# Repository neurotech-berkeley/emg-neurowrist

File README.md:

# emg-neurowrist
Building an EMG-wristband

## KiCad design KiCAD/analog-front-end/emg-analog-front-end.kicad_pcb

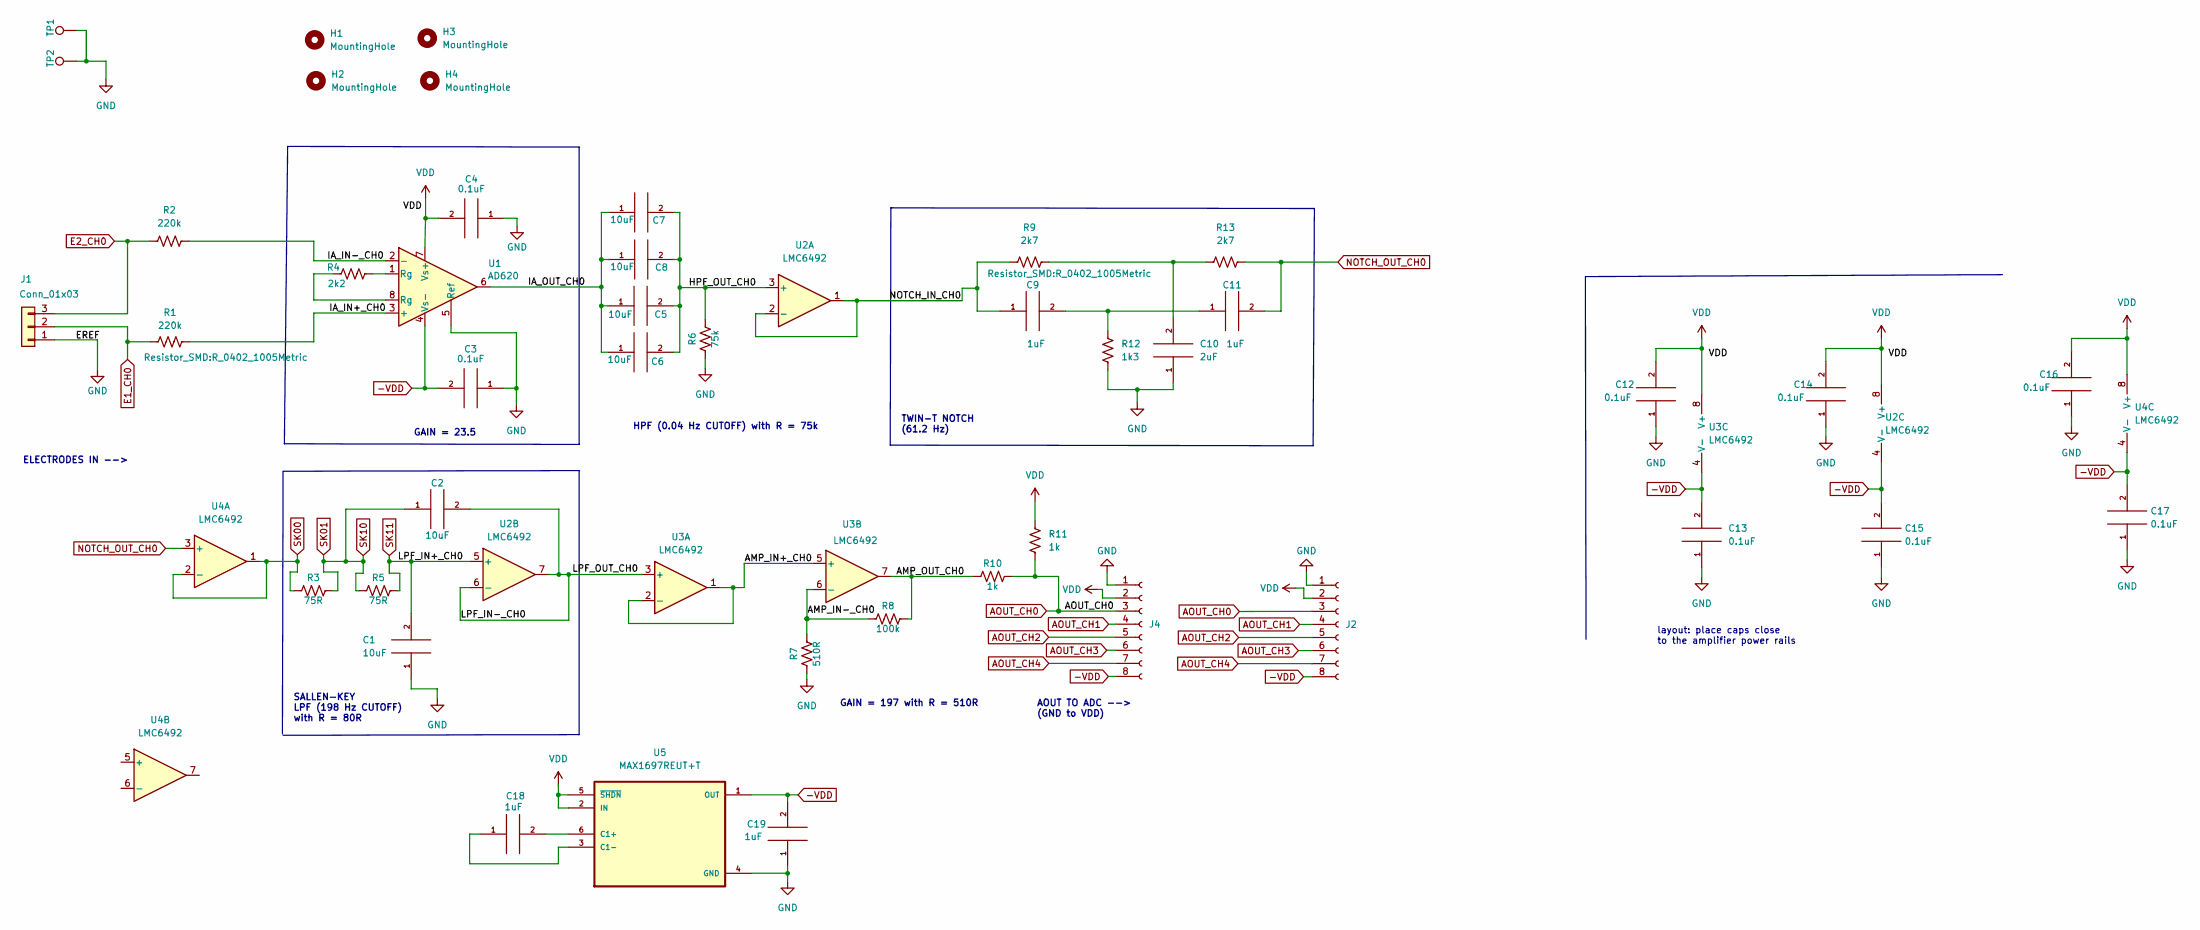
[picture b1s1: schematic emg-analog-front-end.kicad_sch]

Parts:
C1, C2, C5, C6, C7, C8: 10uF; C_0402_1005Metric
C3, C4, C12, C13, C14, C15, C16, C17: 0.1uF; C_0402_1005Metric
C9, C11, C18, C19: 1uF; C_0402_1005Metric
C10: 2uF; C_0402_1005Metric
H1, H2, H3, H4: MountingHole; MountingHole_2.2mm_M2
J1: Conn_01x03; PinHeader_1x03_P1.27mm_Vertical
J2, J4: Conn_01x08_Female; PinHeader_1x08_P1.27mm_Vertical
R1, R2: 220k; R_0402_1005Metric
R3, R5: 75R; R_0402_1005Metric
R4: 2k2; R_0402_1005Metric
R6: 75k; R_0402_1005Metric
R7: 510R; R_0402_1005Metric
R8: 100k; R_0402_1005Metric
R9, R13: 2k7; R_0402_1005Metric
R10, R11: 1k; R_0402_1005Metric
R12: 1k3; R_0402_1005Metric
TP1, TP2: TestPoint; TestPoint_Pad_1.0x1.0mm
U1: AD620; SOIC-8_3.9x4.9mm_P1.27mm
U2, U3, U4: LMC6492; SOIC-8_3.9x4.9mm_P1.27mm
U5: MAX1697REUT+T; SOT95P280X145-6N

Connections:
-VDD: C3.2, C13.2, C15.2, C17.2, C19.2, J2.8, J4.8, U1.4 (Vs-), U2.4 (V-), U3.4 (V-), U4.4 (V-), U5.1 (OUT)
/AMP_IN+_CH0: U3.1, U3.2 (-), U3.5 (+)
/AMP_IN-_CH0: R7.1, R8.2, U3.6 (-)
/AMP_OUT_CH0: R8.1, R10.2, U3.7
/HPF_OUT_CH0: C5.2, C6.2, C7.2, C8.2, R6.1, U2.3 (+)
/IA_IN+_CH0: R1.2, U1.3 (+)
/IA_IN-_CH0: R2.2, U1.2 (-)
/IA_OUT_CH0: C5.1, C6.1, C7.1, C8.1, U1.6
/LPF_IN-_CH0: C2.2, U2.6 (-), U2.7, U3.3 (+)
/NOTCH_IN_CH0: C9.1, R9.2, U2.1, U2.2 (-)
AOUT_CH0: J2.3, J4.3, R10.1, R11.1
AOUT_CH1: J2.4, J4.4
AOUT_CH2: J2.5, J4.5
AOUT_CH3: J2.6, J4.6
AOUT_CH4: J2.7, J4.7
E1_CH0: J1.2, R1.1
E2_CH0: J1.3, R2.1
GND: C1.1, C3.1, C4.1, C10.1, C12.1, C13.1, C14.1, C15.1, C16.1, C17.1, C19.1, J1.1, J2.1, J4.1, R6.2, R7.2, R12.2, TP1.1, TP2.1, U1.5 (Ref), U5.4 (GND)
NOTCH_OUT_CH0: C11.2, R13.1, U4.3 (+)
unnamed: C10.2, R9.1, R13.2
unnamed: C9.2, C11.1, R12.1
unnamed: C18.1, U5.3 (C1-)
unnamed: C18.2, U5.6 (C1+)
unnamed: R4.1, U1.1 (Rg)
unnamed: R4.2, U1.8 (Rg)
SK00: R3.2, U4.1, U4.2 (-)
SK01: C2.1, R3.1, R5.2
SK11: C1.2, R5.1, U2.5 (+)
VDD: C4.2, C12.2, C14.2, C16.2, J2.2, J4.2, R11.2, U1.7 (Vs+), U2.8 (V+), U3.8 (V+), U4.8 (V+), U5.2 (IN), U5.5 (~SHDN)

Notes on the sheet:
GAIN = 23.5
TWIN-T NOTCH (61.2 Hz)
layout: place caps close to the amplifier power rails
HPF (0.04 Hz CUTOFF) with R = 75k
GAIN = 197 with R = 510R
SALLEN-KEY LPF (198 Hz CUTOFF) with R = 80R
ELECTRODES IN -->
AOUT TO ADC --> (GND to VDD)

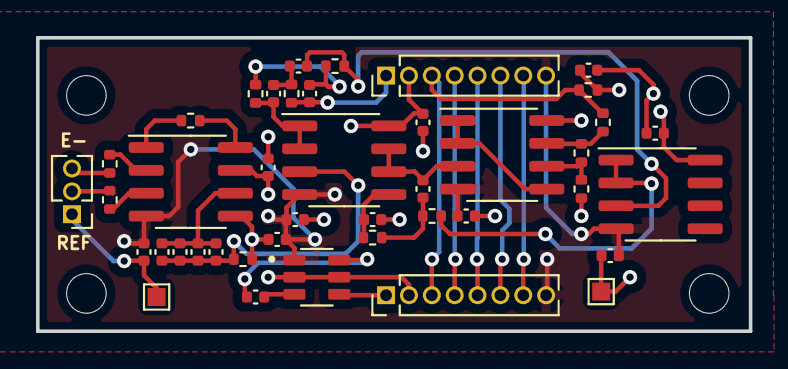
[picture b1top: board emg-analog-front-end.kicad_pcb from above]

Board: 4 copper layers, 39.6 x 16.3 mm, 46 parts (0 on the bottom side), 29 nets.

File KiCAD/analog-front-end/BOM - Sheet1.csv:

Comment,Designator,Footprint,JLCPCB Part #（optional）
"0.1uF, 25V","C3, C4, C12, C13, C14, C15, C16, C17",C_0402_1005Metric,
10uF,"C1, C2, C5, C6, C7, C8",C_0402_1005Metric,
1uF,"C9, C11, C18, C19",C_0402_1005Metric,
2uF,C10,C_0402_1005Metric,
220k,"R1, R2",R_0402_1005Metric,
75R,"R3, R5",R_0402_1005Metric,
2k7,"R9, R13",R_0402_1005Metric,
1k,"R10, R11",R_0402_1005Metric,
2k2,R4,R_0402_1005Metric,
75k,R6,R_0402_1005Metric,
510R,R7,R_0402_1005Metric,
100k,R8,R_0402_1005Metric,
1k3,R12,R_0402_1005Metric,

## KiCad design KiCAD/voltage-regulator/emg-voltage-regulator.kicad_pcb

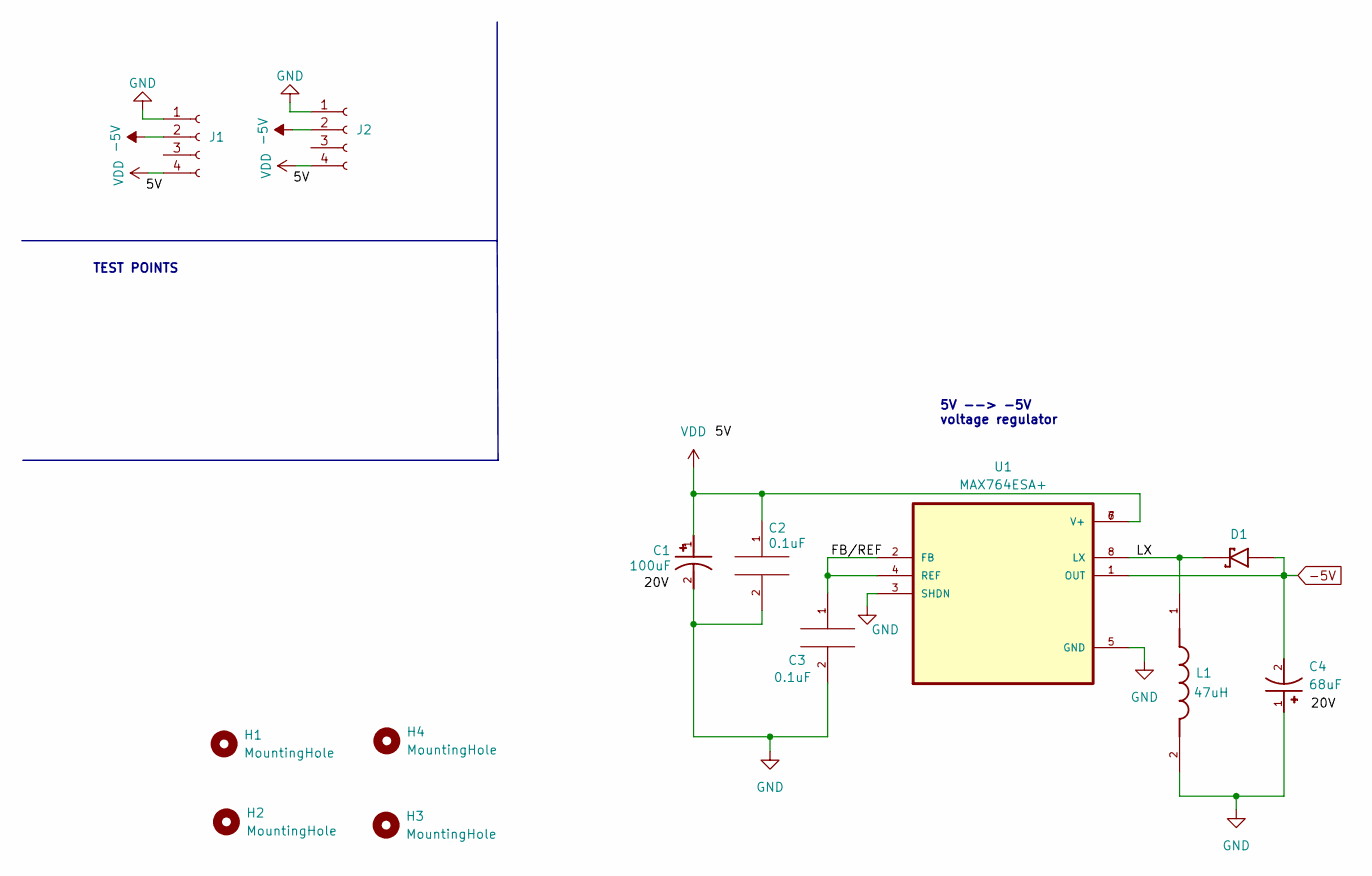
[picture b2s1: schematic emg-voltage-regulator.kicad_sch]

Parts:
C1: 100uF; CAP_20TQC100MYF; PARTREV 30-Nov-20
C2, C3: 0.1uF; C_0603_1608Metric
C4: 68uF; CAP_20TQC100MYF; PARTREV 30-Nov-20
D1: MBRS330T3G; DIOM7959X261N; PARTREV 14
H1, H2, H3, H4: MountingHole; MountingHole_2.2mm_M2
J1, J2: Conn_01x04_Female; PinHeader_1x04_P1.27mm_Vertical
L1: 47uH; IND_NRS6028T470M; PARTREV N/A
U1: MAX764ESA+; SOIC127P600X175-8N

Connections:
-5V: C4.2, D1.A, J1.2, J2.2, U1.1 (OUT)
/FB/REF: C3.1, U1.2 (FB), U1.4 (REF)
/LX: D1.C, L1.1, U1.8 (LX)
GND: C1.2, C2.2, C3.2, C4.1, J1.1, J2.1, L1.2, U1.3 (SHDN), U1.5 (GND)
VDD: C1.1, C2.1, J1.4, J2.4, U1.6 (V+), U1.7 (V+)

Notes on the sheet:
TEST POINTS
5V --> -5V voltage regulator

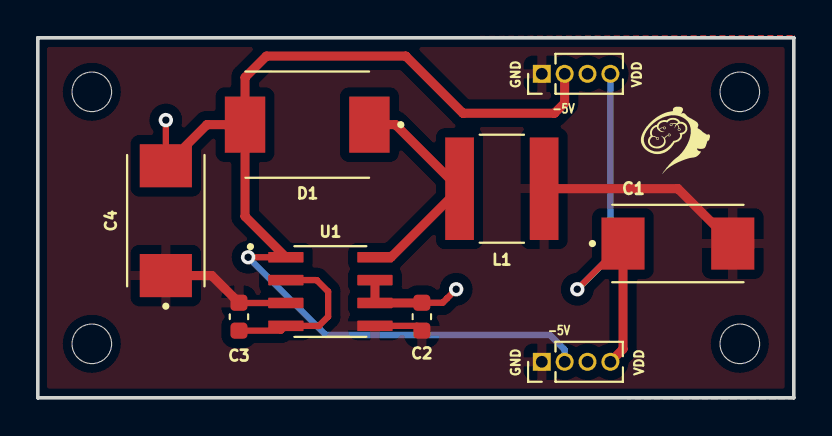
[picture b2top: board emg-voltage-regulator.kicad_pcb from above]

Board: 2 copper layers, 42.0 x 20.0 mm, 13 parts (0 on the bottom side), 5 nets.

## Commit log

2023-03-12 making separate PCBs for analog front-ends
2023-03-13 more progress on layout
2023-03-13 AFE sub-circuit layout done
2023-03-13 layout for voltage regulator done
2023-03-13 added VSS input to the AFE board
2023-03-13 adding production files
2023-03-22 small fixes, dimensions
2023-03-26 first draft of the real-time signal-recording dashboard
2023-03-27 preliminary real-time streaming is working
2023-03-27 automatic save to csv files should work
2023-04-18 modifying the pcb for new electrode placement and replacing op amps
2023-04-20 added mounting hole plates for electrodes and replaced op-amp and voltage regulator ICs
2023-04-20 DRC passing, should be all good for starting fab files
2023-04-20 adding fabrication files
2023-08-20 replaced temporary resistor holders and added voltage inverter IC
2023-08-21 v3 layout done
2023-10-02 adding basic signal scripts
2024-01-29 swapped out the amplifier to ad8421
2024-02-24 test
